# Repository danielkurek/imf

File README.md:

# Interactive mesh framework (IMF)

Framework for interactive distributed network of luminous devices. Devices are based on ESP32-S3. Framework was developed as part of bachelor thesis at Charles University Faculty of Mathematics and Physics (Prague, Czech Republic).

Author: Daniel Kurek 09.05.2024

## Folder structure

- `boards` - source files for devices designed for this framework (official dev modules can also be used)
- `distance-analysis` - analysis of WiFi FTM distance measurement (with measured data)
- `mesh-visualizer` - helper application for visualization of positions of devices and control states of devices through Bluetooth mesh
- `result` - results from testing of the framework on example application
- `src` - source code of the framework

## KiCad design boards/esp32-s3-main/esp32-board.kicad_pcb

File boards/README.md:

# Boards

Boards were designed in KiCAD 7 (then converted to KiCAD 8). In folders `esp32-s3-main` and `esp32-s3-simple` are source files for boards along with exported schematics to PDF, exported BOM and gerbers ready for manufacturing.

`esp32-s3-main` contains board that is used in this work as main module and `esp32-s3-simple` is used as secondary module.

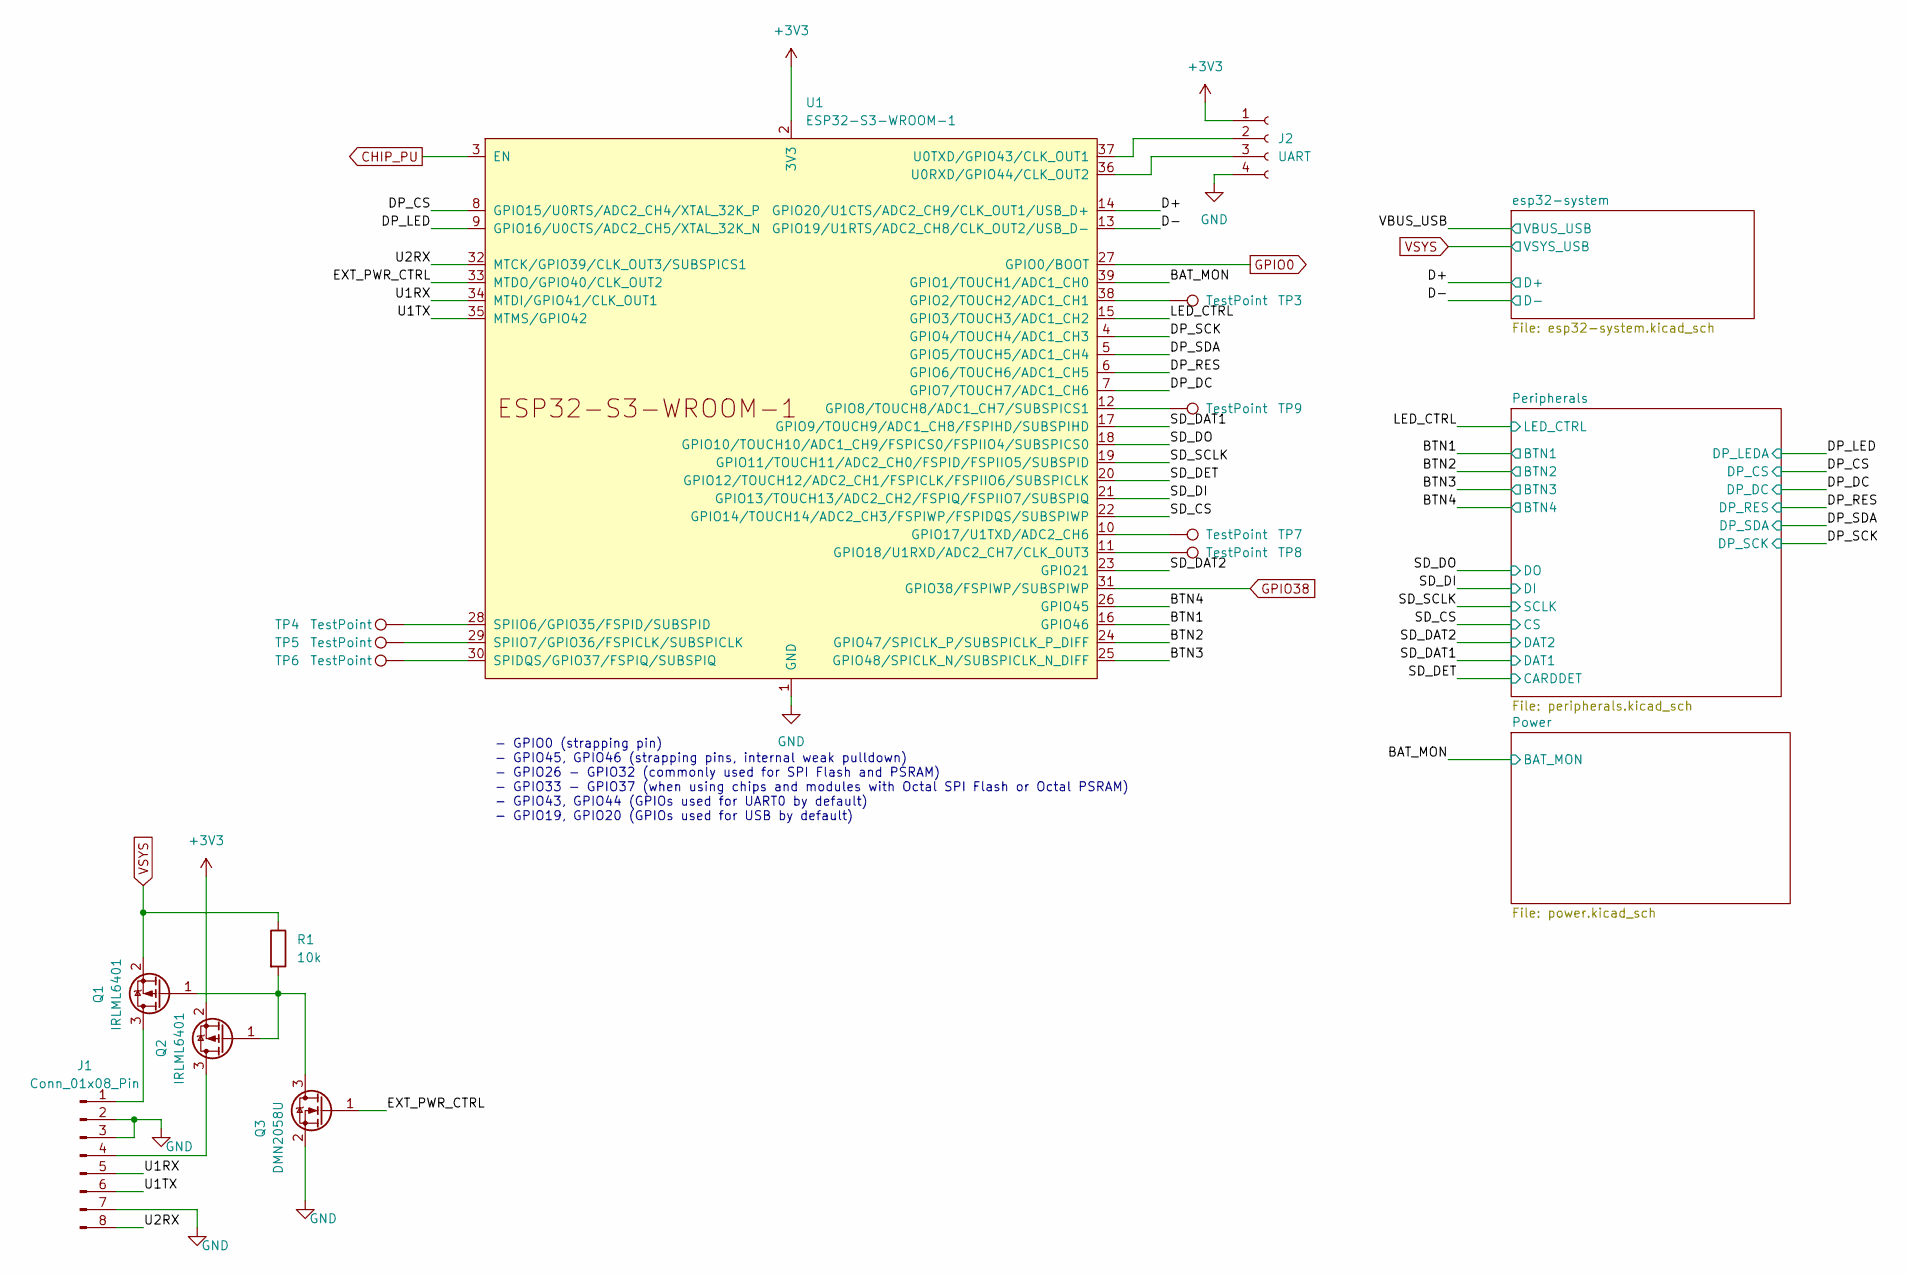
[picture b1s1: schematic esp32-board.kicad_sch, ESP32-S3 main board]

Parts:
J1: Conn_01x08_Pin; PinSocket_1x08_P2.54mm_Vertical
J2: UART; PinSocket_1x04_P2.54mm_Vertical
Q1, Q2: IRLML6401; SOT-23
Q3: DMN2058U; SOT-23
R1: 10k; R_1206_3216Metric_Pad1.30x1.75mm_HandSolder
TP3, TP4, TP5, TP6, TP7, TP8, TP9: TestPoint; TestPoint_Pad_1.0x1.0mm
U1: ESP32-S3-WROOM-1

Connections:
+3V3: J2.1, Q2.2 (S), U1.2 (3V3); also elsewhere on the board
/BAT_MON: U1.39 (GPIO1/TOUCH1/ADC1_CH0); also elsewhere on the board
/BTN1: U1.16 (GPIO46); also elsewhere on the board
/BTN2: U1.24 (GPIO47/SPICLK_P/SUBSPICLK_P_DIFF); also elsewhere on the board
/BTN3: U1.25 (GPIO48/SPICLK_N/SUBSPICLK_N_DIFF); also elsewhere on the board
/BTN4: U1.26 (GPIO45); also elsewhere on the board
/D+: U1.14 (GPIO20/U1CTS/ADC2_CH9/CLK_OUT1/USB_D+); also elsewhere on the board
/D-: U1.13 (GPIO19/U1RTS/ADC2_CH8/CLK_OUT2/USB_D-); also elsewhere on the board
/DP_CS: U1.8 (GPIO15/U0RTS/ADC2_CH4/XTAL_32K_P); also elsewhere on the board
/DP_DC: U1.7 (GPIO7/TOUCH7/ADC1_CH6); also elsewhere on the board
/DP_LED: U1.9 (GPIO16/U0CTS/ADC2_CH5/XTAL_32K_N); also elsewhere on the board
/DP_RES: U1.6 (GPIO6/TOUCH6/ADC1_CH5); also elsewhere on the board
/DP_SCK: U1.4 (GPIO4/TOUCH4/ADC1_CH3); also elsewhere on the board
/DP_SDA: U1.5 (GPIO5/TOUCH5/ADC1_CH4); also elsewhere on the board
/EXT_PWR_CTRL: Q3.1 (G), U1.33 (MTDO/GPIO40/CLK_OUT2)
/LED_CTRL: U1.15 (GPIO3/TOUCH3/ADC1_CH2); also elsewhere on the board
/SD_CS: U1.22 (GPIO14/TOUCH14/ADC2_CH3/FSPIWP/FSPIDQS/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); also elsewhere on the board
/SD_DAT1: U1.17 (GPIO9/TOUCH9/ADC1_CH8/FSPIHD/SUBSPIHD); also elsewhere on the board
/SD_DAT2: U1.23 (GPIO21); also elsewhere on the board
/SD_DET: U1.20 (GPIO12/TOUCH12/ADC2_CH1/FSPICLK/FSPIIO6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); also elsewhere on the board
/SD_DI: U1.21 (GPIO13/TOUCH13/ADC2_CH2/FSPIQ/FSPIIO7/S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); also elsewhere on the board
/SD_DO: U1.18 (GPIO10/TOUCH10/ADC1_CH9/FSPICS0/FSPIIO4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); also elsewhere on the board
/SD_SCLK: U1.19 (GPIO11/TOUCH11/ADC2_CH0/FSPID/FSPIIO5/S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); also elsewhere on the board
/U1RX: J1.5, U1.34 (MTDI/GPIO41/CLK_OUT1)
/U1TX: J1.6, U1.35 (MTMS/GPIO42)
/U2RX: J1.8, U1.32 (MTCK/GPIO39/CLK_OUT3/SUBSPICS1)
CHIP_PU: U1.3 (EN); also elsewhere on the board
GND: J1.2, J1.3, J1.7, J2.4, Q3.2 (S), U1.1 (GND), U1.40 (GND), U1.41 (GND); also elsewhere on the board
GPIO0: U1.27 (GPIO0/BOOT); also elsewhere on the board
GPIO38: U1.31 (GPIO38/FSPIWP/SUBSPIWP); also elsewhere on the board
unnamed: J1.1, Q1.3 (D)
unnamed: J1.4, Q2.3 (D)
unnamed: J2.2, U1.37 (U0TXD/GPIO43/CLK_OUT1)
unnamed: J2.3, U1.36 (U0RXD/GPIO44/CLK_OUT2)
unnamed: Q1.1 (G), Q2.1 (G), Q3.3 (D), R1.2
unnamed: TP3.1, U1.38 (GPIO2/TOUCH2/ADC1_CH1)
unnamed: TP9.1, U1.12 (GPIO8/TOUCH8/ADC1_CH7/SUBSPICS1)
unnamed: TP7.1, U1.10 (GPIO17/U1TXD/ADC2_CH6)
unnamed: TP8.1, U1.11 (GPIO18/U1RXD/ADC2_CH7/CLK_OUT3)
unnamed: TP6.1, U1.30 (SPIDQS/GPIO37/FSPIQ/SUBSPIQ)
unnamed: TP4.1, U1.28 (SPIIO6/GPIO35/FSPID/SUBSPID)
unnamed: TP5.1, U1.29 (SPIIO7/GPIO36/FSPICLK/SUBSPICLK)
VSYS: Q1.2 (S), R1.1; also elsewhere on the board

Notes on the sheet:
- GPIO0 (strapping pin) - GPIO45, GPIO46 (strapping pins, internal weak pulldown) - GPIO26 - GPIO32 (commonly used for SPI Flash and PSRAM) - GPIO33 - GPIO37 (when using chips and modules with Octal SPI Flash or Octal PSRAM) - GPIO43, GPIO44 (GPIOs used for UART0 by default) - GPIO19, GPIO20 (GPIOs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

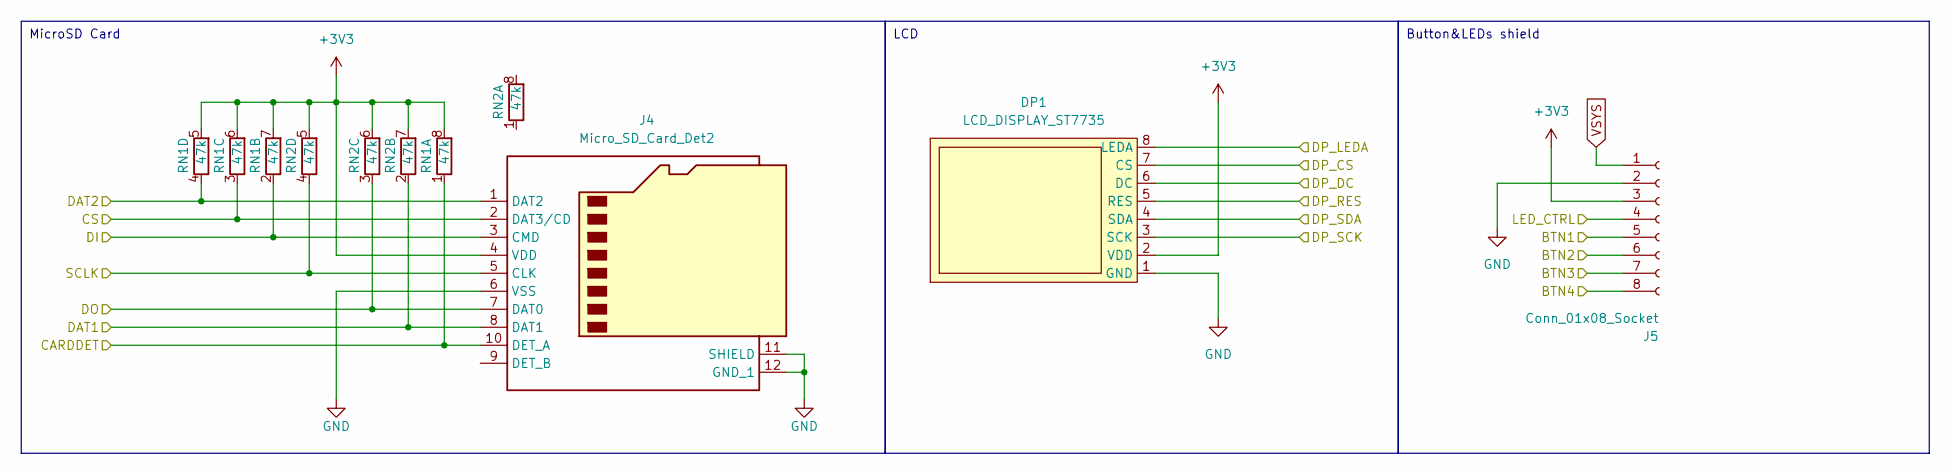
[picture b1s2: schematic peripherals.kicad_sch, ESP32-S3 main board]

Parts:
DP1: LCD_DISPLAY_ST7735; PinSocket_1x08_P2.54mm_Vertical
J4: Micro_SD_Card_Det2; GCT_MEM2061-01-188-00-A_REVA
J5: Conn_01x08_Socket; PinSocket_1x08_P2.54mm_Vertical
RN1, RN2: 47k; R_Array_Convex_4x1206

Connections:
+3V3: DP1.2 (VDD), J4.4 (VDD), J5.3, RN1.5 (R4.2), RN1.6 (R3.2), RN1.7 (R2.2), RN1.8 (R1.2), RN2.5 (R4.2), RN2.6 (R3.2), RN2.7 (R2.2); also elsewhere on the board
/BTN1: J5.5; also elsewhere on the board
/BTN2: J5.6; also elsewhere on the board
/BTN3: J5.7; also elsewhere on the board
/BTN4: J5.8; also elsewhere on the board
/DP_CS: DP1.7 (CS); also elsewhere on the board
/DP_DC: DP1.6 (DC); also elsewhere on the board
/DP_LED: DP1.8 (LEDA); also elsewhere on the board
/DP_RES: DP1.5 (RES); also elsewhere on the board
/DP_SCK: DP1.3 (SCK); also elsewhere on the board
/DP_SDA: DP1.4 (SDA); also elsewhere on the board
/LED_CTRL: J5.4; also elsewhere on the board
/SD_CS: J4.2 (DAT3/CD), RN1.3 (R3.1); also elsewhere on the board
/SD_DAT1: J4.8 (DAT1), RN2.2 (R2.1); also elsewhere on the board
/SD_DAT2: J4.1 (DAT2), RN1.4 (R4.1); also elsewhere on the board
/SD_DET: J4.10 (DET_A), RN1.1 (R1.1); also elsewhere on the board
/SD_DI: J4.3 (CMD), RN1.2 (R2.1); also elsewhere on the board
/SD_DO: J4.7 (DAT0), RN2.3 (R3.1); also elsewhere on the board
/SD_SCLK: J4.5 (CLK), RN2.4 (R4.1); also elsewhere on the board
GND: DP1.1 (GND), J4.6 (VSS), J4.11 (SHIELD), J4.12 (GND_1), J5.2; also elsewhere on the board
VSYS: J5.1; also elsewhere on the board

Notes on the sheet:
Button&LEDs shield
MicroSD Card
LCD

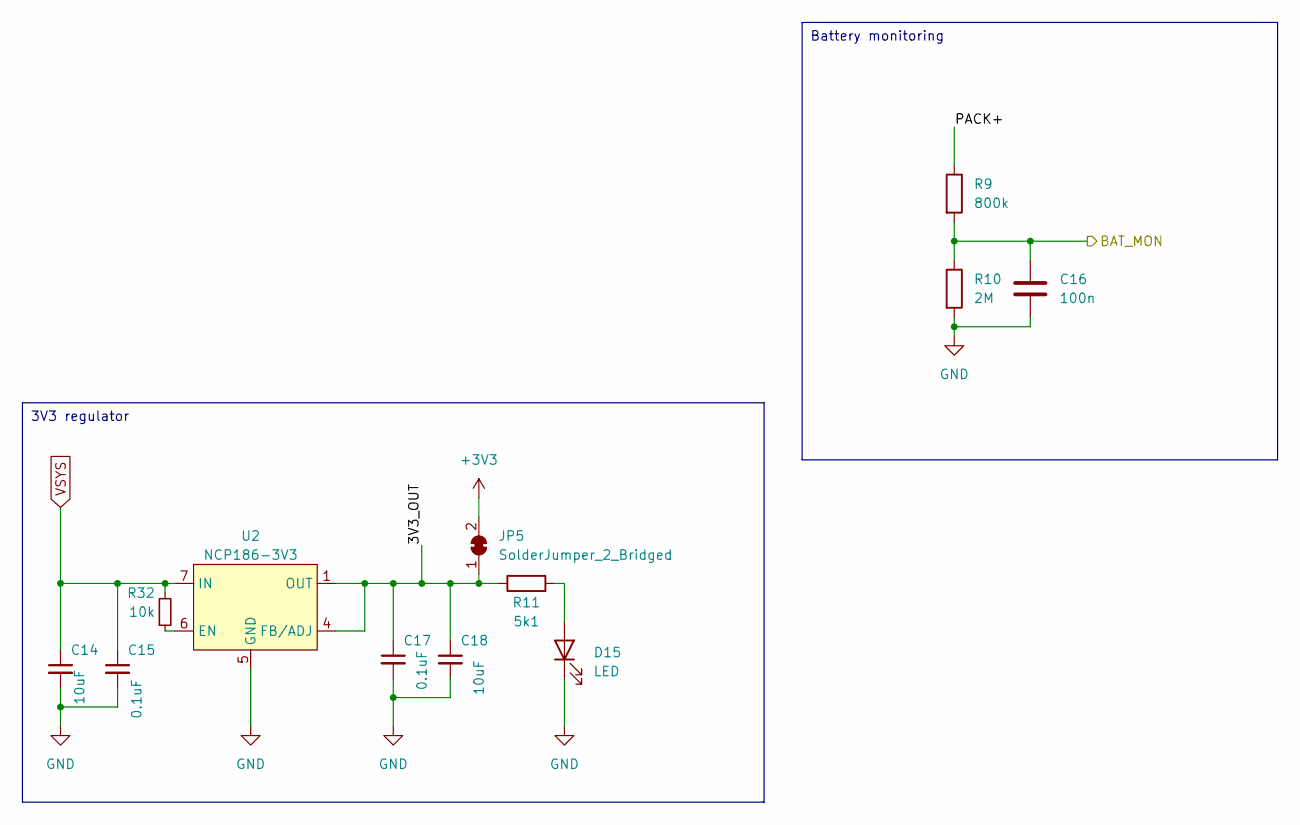
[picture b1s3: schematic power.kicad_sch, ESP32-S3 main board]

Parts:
C14, C18: 10uF; C_1206_3216Metric_Pad1.33x1.80mm_HandSolder; Rating 50V; Tolerance 10%
C15, C17: 0.1uF; C_0603_1608Metric_Pad1.08x0.95mm_HandSolder; Rating 50V; Tolerance 10%
C16: 100n; C_0603_1608Metric_Pad1.08x0.95mm_HandSolder
D15: LED; LED_0805_2012Metric_Pad1.15x1.40mm_HandSolder
JP5: SolderJumper_2_Bridged; SolderJumper-2_P1.3mm_Bridged2Bar_Pad1.0x1.5mm
R9: 800k; R_1206_3216Metric_Pad1.30x1.75mm_HandSolder
R10: 2M; R_1206_3216Metric_Pad1.30x1.75mm_HandSolder
R11: 5k1; R_1206_3216Metric_Pad1.30x1.75mm_HandSolder
R32: 10k; R_1206_3216Metric_Pad1.30x1.75mm_HandSolder
U2: NCP186-3V3; XDFN8

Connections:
+3V3: JP5.2 (B); also elsewhere on the board
/BAT_MON: C16.1, R9.2, R10.1; also elsewhere on the board
/Power/3V3_OUT: C17.1, C18.1, JP5.1 (A), R11.1, U2.1 (OUT), U2.2 (OUT), U2.4 (FB/ADJ)
/Power/PACK+: R9.1
GND: C14.2, C15.2, C16.2, C17.2, C18.2, D15.1 (K), R10.2, U2.5 (GND), U2.EPAD (GND); also elsewhere on the board
unnamed: D15.2 (A), R11.2
unnamed: R32.1, U2.6 (EN)
VSYS: C14.1, C15.1, R32.2, U2.7 (IN), U2.8 (IN); also elsewhere on the board

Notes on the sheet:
3V3 regulator
Battery monitoring

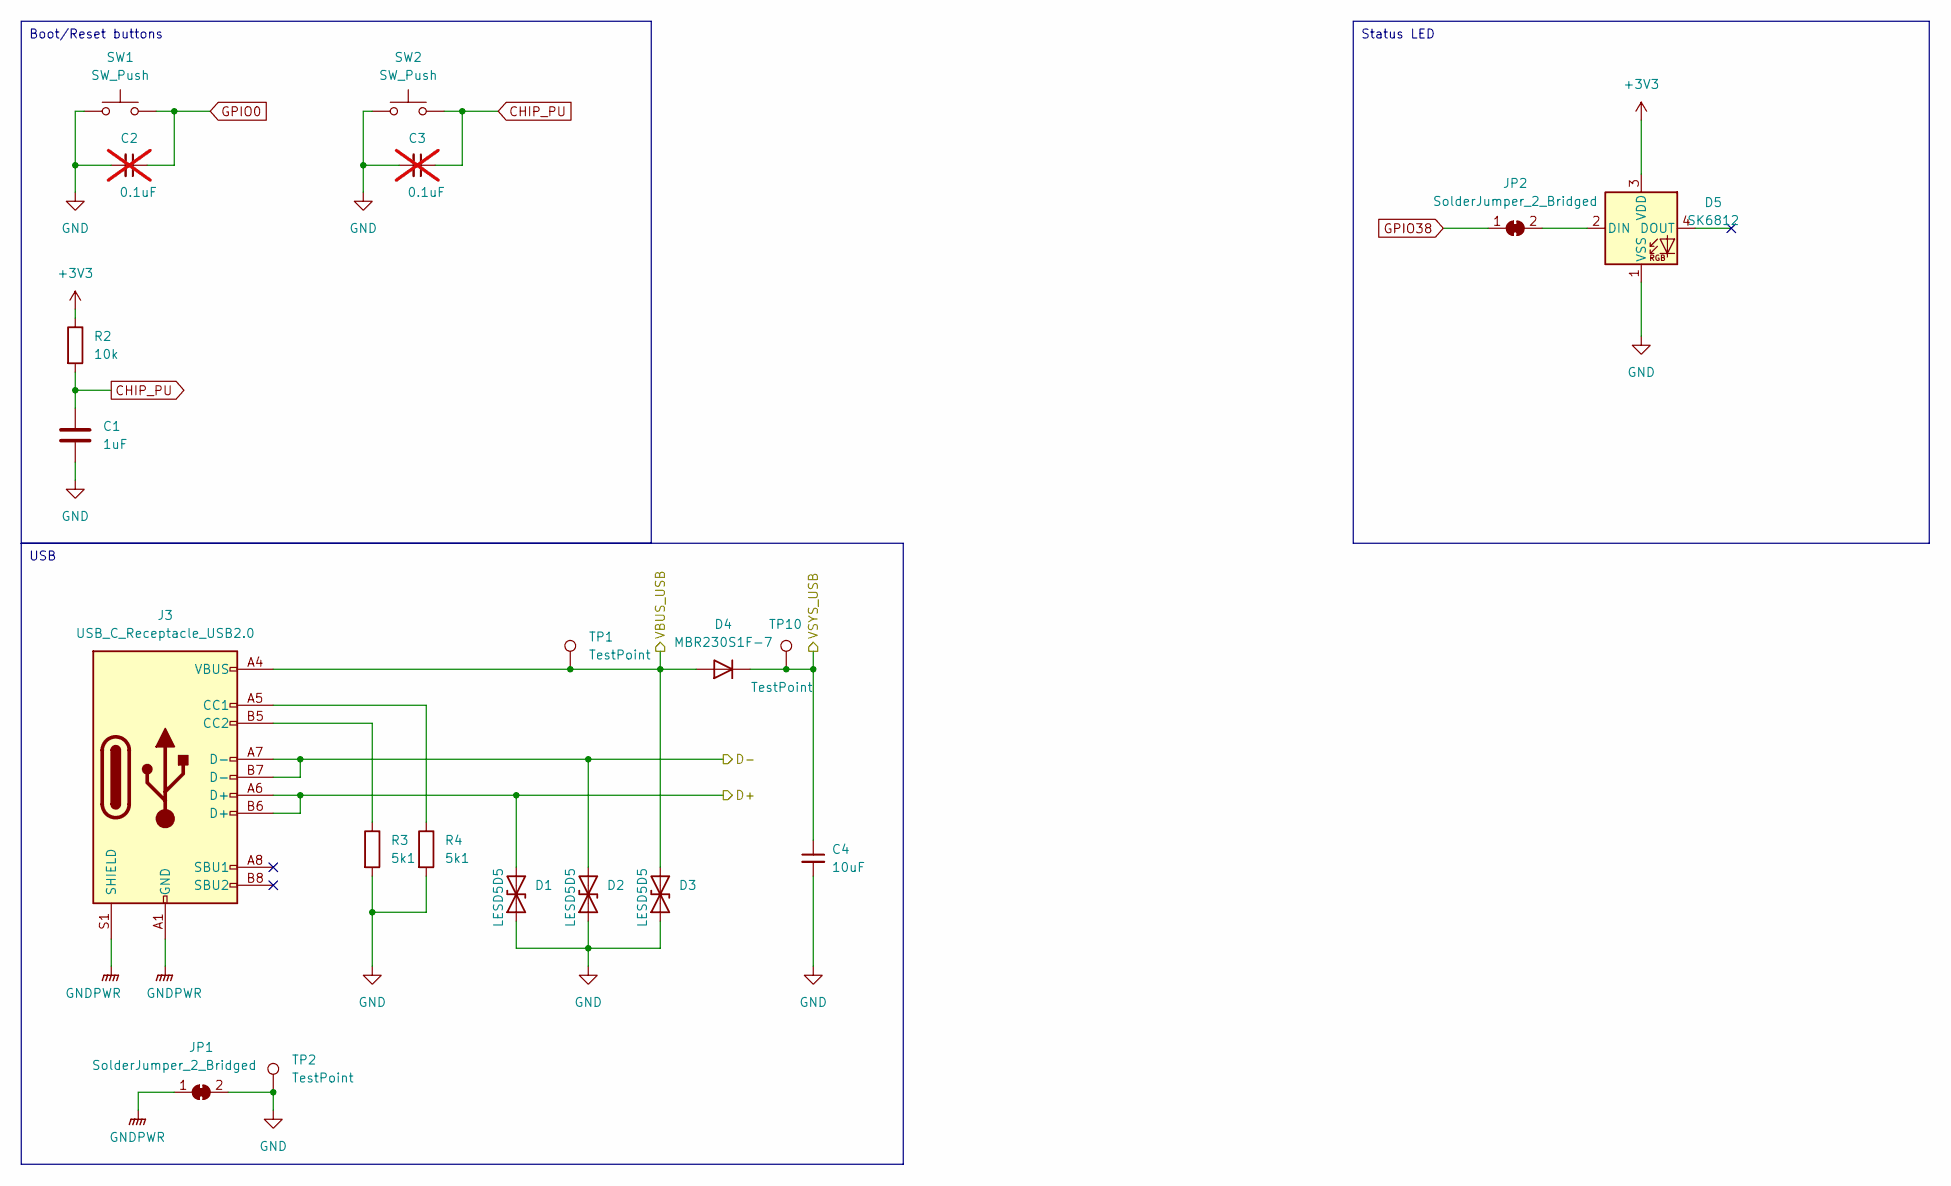
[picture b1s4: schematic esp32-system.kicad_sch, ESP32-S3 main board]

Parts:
C1: 1uF; C_0603_1608Metric_Pad1.08x0.95mm_HandSolder
C2, C3: 0.1uF; C_0603_1608Metric_Pad1.08x0.95mm_HandSolder; Rating 50V; Tolerance 10%; not fitted
C4: 10uF; C_1206_3216Metric_Pad1.33x1.80mm_HandSolder; Rating 25V; Tolerance 20%
D1, D2, D3: LESD5D5; D_SOD-323_HandSoldering
D4: MBR230S1F-7; D_SOD-123F
D5: SK6812; LED_SK6812_PLCC4_5.0x5.0mm_P3.2mm
J3: USB_C_Receptacle_USB2.0; USB_C_Receptacle_GCT_USB4105-xx-A_16P_TopMnt_Horizontal
JP1, JP2: SolderJumper_2_Bridged; SolderJumper-2_P1.3mm_Bridged2Bar_Pad1.0x1.5mm
R2: 10k; R_1206_3216Metric_Pad1.30x1.75mm_HandSolder
R3, R4: 5k1; R_1206_3216Metric_Pad1.30x1.75mm_HandSolder
SW1, SW2: SW_Push; SW_PUSH_6mm
TP1, TP2, TP10: TestPoint; TestPoint_Pad_1.0x1.0mm

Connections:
+3V3: D5.3 (VDD), R2.1; also elsewhere on the board
/D+: D1.2 (A2), J3.A6 (D+), J3.B6 (D+); also elsewhere on the board
/D-: D2.2 (A2), J3.A7 (D-), J3.B7 (D-); also elsewhere on the board
/VBUS_USB: D3.2 (A2), D4.2 (A), J3.A4 (VBUS), J3.A9 (VBUS), J3.B4 (VBUS), J3.B9 (VBUS), TP1.1
CHIP_PU: C1.1, C3.1, R2.2, SW2.2; also elsewhere on the board
GND: C1.2, C2.2, C3.2, C4.2, D1.1 (A1), D2.1 (A1), D3.1 (A1), D5.1 (VSS), JP1.2 (B), R3.2, R4.2, SW1.1, SW2.1, TP2.1; also elsewhere on the board
GNDPWR: J3.A1 (GND), J3.A12 (GND), J3.B1 (GND), J3.B12 (GND), J3.S1 (SHIELD), JP1.1 (A)
GPIO0: C2.1, SW1.2; also elsewhere on the board
GPIO38: JP2.1 (A); also elsewhere on the board
unnamed: D5.2 (DIN), JP2.2 (B)
unnamed: J3.A5 (CC1), R4.1
unnamed: J3.B5 (CC2), R3.1
VSYS: C4.1, D4.1 (K), TP10.1; also elsewhere on the board

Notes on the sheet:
Status LED
USB
Boot/Reset buttons

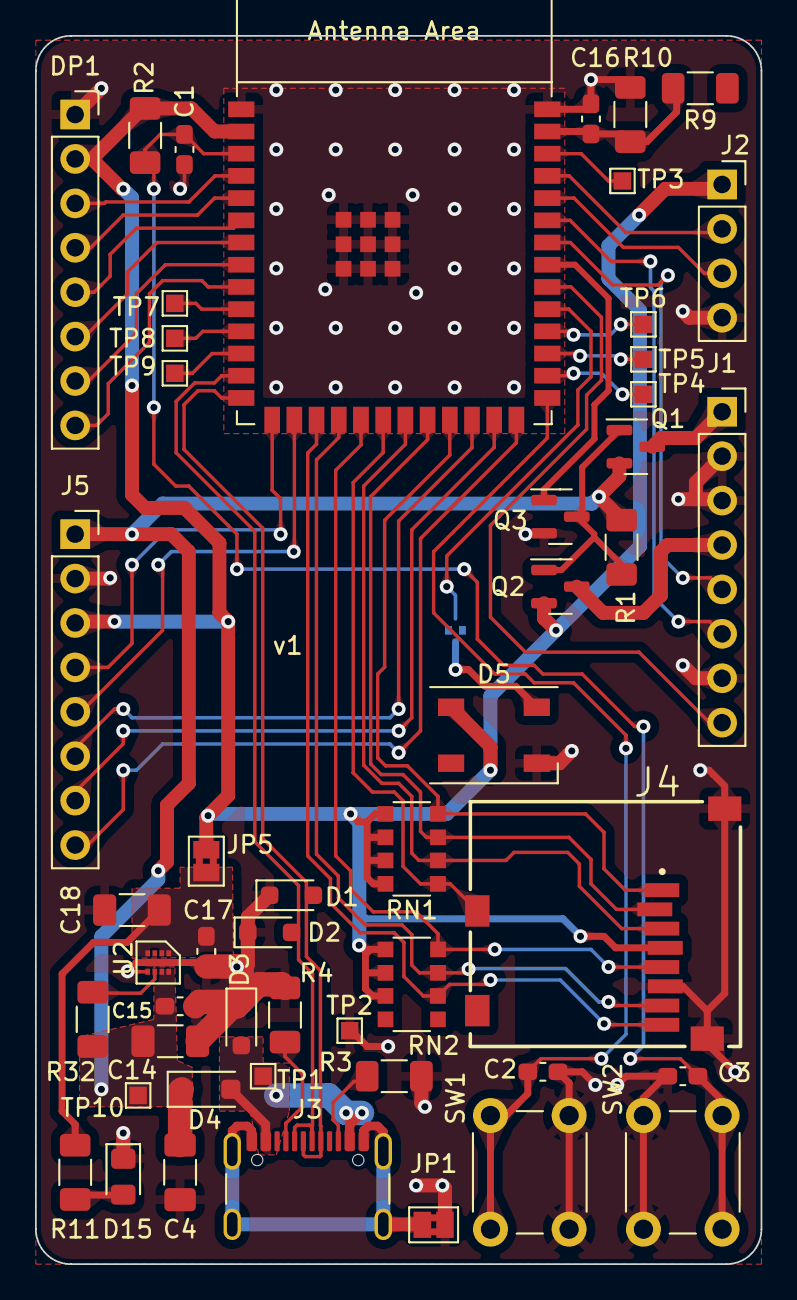
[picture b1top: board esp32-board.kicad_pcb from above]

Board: 2 copper layers, 41.5 x 70.2 mm, 51 parts (1 on the bottom side), 51 nets.

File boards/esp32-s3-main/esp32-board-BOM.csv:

"Source:","/home/dk/Projects/KiCAD projects/esp32-board/esp32-board.kicad_sch"
"Date:","Tue 26 Mar 2024 17:12:36 CET"
"Tool:","Eeschema 7.0.11-2.fc39"
"Generator:","/usr/share/kicad/plugins/bom_csv_grouped_by_value.py"
"Component Count:","51"

"Collated Components:"

"Item","Qty","Reference(s)","Value","LibPart","Footprint","Datasheet","DNP","Rating","Sim.Device","Sim.Pins","Tolerance"
"1","1","C1","1uF","Device:C","Capacitor_SMD:C_0603_1608Metric_Pad1.08x0.95mm_HandSolder","~","","","","",""
"2","2","C2, C3","0.1uF","Device:C_Small","Capacitor_SMD:C_0603_1608Metric_Pad1.08x0.95mm_HandSolder","~","DNP","50V","","","10%"
"3","3","C4, C14, C18","10uF","Device:C_Small","Capacitor_SMD:C_1206_3216Metric_Pad1.33x1.80mm_HandSolder","~","","25V","","","20%"
"4","2","C15, C17","0.1uF","Device:C_Small","Capacitor_SMD:C_0603_1608Metric_Pad1.08x0.95mm_HandSolder","~","","50V","","","10%"
"5","1","C16","100n","Device:C","Capacitor_SMD:C_0603_1608Metric_Pad1.08x0.95mm_HandSolder","~","","","","",""
"6","3","D1, D2, D3","LESD5D5","Device:D_TVS","Diode_SMD:D_SOD-323_HandSoldering","~","","","","",""
"7","1","D4","MBR230S1F-7 ","Device:D","Diode_SMD:D_SOD-123F","~","","","D","1=K 2=A",""
"8","1","D5","SK6812","LED:SK6812","LED_SMD:LED_SK6812_PLCC4_5.0x5.0mm_P3.2mm","https://cdn-shop.adafruit.com/product-files/1138/SK6812+LED+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","","","","",""
"9","1","D15","LED","Device:LED","LED_SMD:LED_0805_2012Metric_Pad1.15x1.40mm_HandSolder","~","","","","",""
"10","1","DP1","LCD_DISPLAY_ST7735","Custom_lib:LCD_DISPLAY_ST7735","Connector_PinSocket_2.54mm:PinSocket_1x08_P2.54mm_Vertical","","","","","",""
"11","1","J1","Conn_01x08_Pin","Connector:Conn_01x08_Pin","Connector_PinSocket_2.54mm:PinSocket_1x08_P2.54mm_Vertical","~","","","","",""
"12","1","J2","UART","Connector:Conn_01x04_Socket","Connector_PinSocket_2.54mm:PinSocket_1x04_P2.54mm_Vertical","~","","","","",""
"13","1","J3","USB_C_Receptacle_USB2.0","Connector:USB_C_Receptacle_USB2.0","Connector_USB:USB_C_Receptacle_GCT_USB4105-xx-A_16P_TopMnt_Horizontal","https://www.usb.org/sites/default/files/documents/usb_type-c.zip","","","","",""
"14","1","J4","Micro_SD_Card_Det2",":Micro_SD_Card_Det2_1","GCT_MEM2061:GCT_MEM2061-01-188-00-A_REVA","https://gct.co/pdfjs/web/viewer.html?file=/files/specs/MEM20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","","","","",""
"15","1","J5","Conn_01x08_Socket","Connector:Conn_01x08_Socket","Connector_PinSocket_2.54mm:PinSocket_1x08_P2.54mm_Vertical","~","","","","",""
"16","3","JP1, JP2, JP5","SolderJumper_2_Bridged","Jumper:SolderJumper_2_Bridged","Jumper:SolderJumper-2_P1.3mm_Bridged2Bar_Pad1.0x1.5mm","~","","","","",""
"17","2","Q1, Q2","IRLML6401","Transistor_FET:IRLML6401","Package_TO_SOT_SMD:SOT-23","https://www.infineon.com/dgdl/irlml6401pbf.pdf?fileId=5546d4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","","","","",""
"18","1","Q3","DMN2058U","Transistor_FET:DMN2058U","Package_TO_SOT_SMD:SOT-23","http://www.diodes.com/assets/Datasheets/DMN2058U.pdf","","","","",""
"19","2","R1, R2","10k","Device:R","Resistor_SMD:R_1206_3216Metric_Pad1.30x1.75mm_HandSolder","~","","","","",""
"20","3","R3, R4, R11","5k1","Device:R","Resistor_SMD:R_1206_3216Metric_Pad1.30x1.75mm_HandSolder","~","","","","",""
"21","1","R9","800k","Device:R","Resistor_SMD:R_1206_3216Metric_Pad1.30x1.75mm_HandSolder","~","","","","",""
"22","1","R10","2M","Device:R","Resistor_SMD:R_1206_3216Metric_Pad1.30x1.75mm_HandSolder","~","","","","",""
"23","1","R32","10k","Device:R_Small","Resistor_SMD:R_1206_3216Metric_Pad1.30x1.75mm_HandSolder","~","","","","",""
"24","2","RN1, RN2","47k","Device:R_Pack04_Split","Resistor_SMD:R_Array_Convex_4x1206","~","","","","",""
"25","2","SW1, SW2","SW_Push","Switch:SW_Push","Button_Switch_THT:SW_PUSH_6mm","~","","","","",""
"26","10","TP1, TP2, TP3, TP4, TP5, TP6, TP7, TP8, TP9, TP10","TestPoint","Connector:TestPoint","TestPoint:TestPoint_Pad_1.0x1.0mm","~","","","","",""
"27","1","U1","ESP32-S3-WROOM-1","PCM_Espressif:ESP32-S3-WROOM-1","PCM_Espressif:ESP32-S3-WROOM-1","https://www.espressif.com/sites/default/files/documentation/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","","","","",""
"28","1","U2","NCP186-3V3","Custom_lib:NCP186-3V3","Custom:XDFN8","https://www.onsemi.com/pdf/datasheet/ncp186-d.pdf","","","","",""

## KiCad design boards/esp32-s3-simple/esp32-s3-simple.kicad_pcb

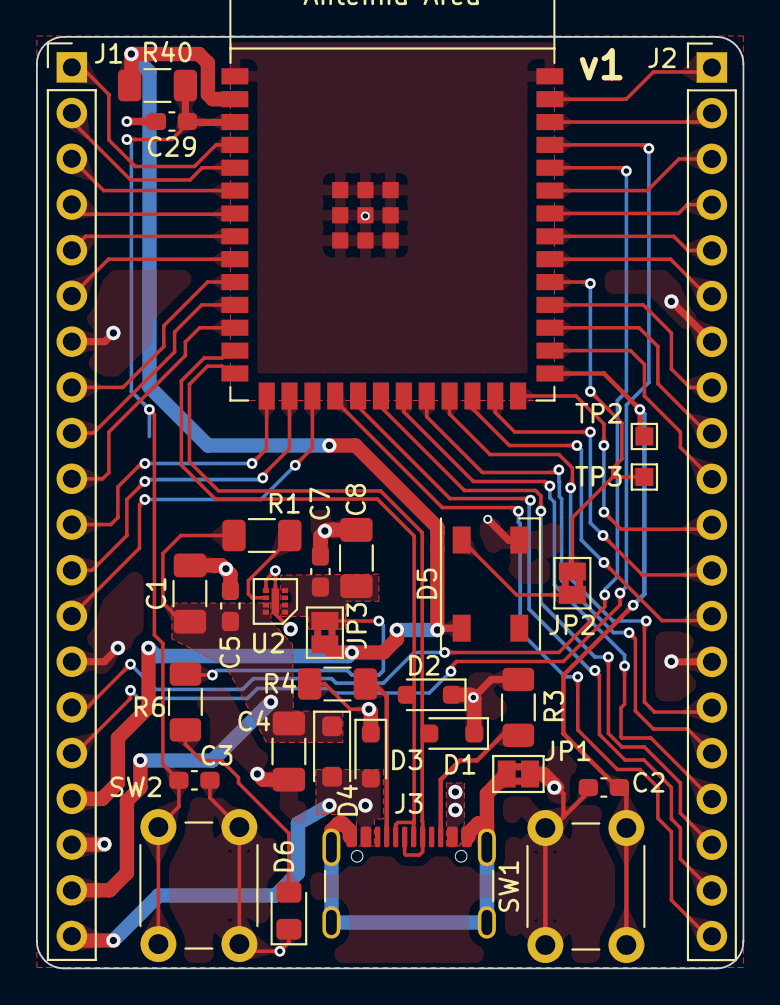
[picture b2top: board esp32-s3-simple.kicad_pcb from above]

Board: 2 copper layers, 39.2 x 51.8 mm, 32 parts (1 on the bottom side), 48 nets.

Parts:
C1, C4, C8: 10uF; C_1206_3216Metric_Pad1.33x1.80mm_HandSolder
C2, C3, C5, C7: 0.1uF; C_0603_1608Metric_Pad1.08x0.95mm_HandSolder
C29: 1uF; C_0603_1608Metric_Pad1.08x0.95mm_HandSolder
D1, D2, D3: LESD5D5; D_SOD-323_HandSoldering
D4: MBR230S1F-7; D_SOD-123F
D5: SK6812; LED_SK6812_PLCC4_5.0x5.0mm_P3.2mm
D6: LED; LED_0805_2012Metric_Pad1.15x1.40mm_HandSolder
J1, J2: Conn_01x20_Pin; PinHeader_1x20_P2.54mm_Vertical
J3: USB_C_Receptacle_USB2.0; USB_C_Receptacle_GCT_USB4105-xx-A_16P_TopMnt_Horizontal
JP1, JP2, JP3: SolderJumper_2_Bridged; SolderJumper-2_P1.3mm_Bridged2Bar_Pad1.0x1.5mm
R1, R40: 10k; R_1206_3216Metric_Pad1.30x1.75mm_HandSolder
R3, R4, R6: 5k1; R_1206_3216Metric_Pad1.30x1.75mm_HandSolder
SW1, SW2: SW_Push; SW_PUSH_6mm
TP1, TP2, TP3: TestPoint; TestPoint_Pad_1.0x1.0mm
U1: ESP32-S3-WROOM-1
U2: NCP186-3V3; XDFN8

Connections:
+3V3: D5.3 (VDD), J1.17, JP3.2 (B), R40.1, U1.2 (3V3)
/D+: D1.2 (A2), J3.A6 (D+), J3.B6 (D+), U1.14 (GPIO20/U1CTS/ADC2_CH9/CLK_OUT1/USB_D+)
/D-: D2.2 (A2), J3.A7 (D-), J3.B7 (D-), U1.13 (GPIO19/U1RTS/ADC2_CH8/CLK_OUT2/USB_D-)
/GPIO1: J2.1, U1.39 (GPIO1/TOUCH1/ADC1_CH0)
/GPIO2: J2.2, U1.38 (GPIO2/TOUCH2/ADC1_CH1)
/GPIO3: J1.11, U1.15 (GPIO3/TOUCH3/ADC1_CH2)
/GPIO4: J1.1, U1.4 (GPIO4/TOUCH4/ADC1_CH3)
/GPIO5: J1.2, U1.5 (GPIO5/TOUCH5/ADC1_CH4)
/GPIO6: J1.3, U1.6 (GPIO6/TOUCH6/ADC1_CH5)
/GPIO7: J1.4, U1.7 (GPIO7/TOUCH7/ADC1_CH6)
/GPIO8: J1.10, U1.12 (GPIO8/TOUCH8/ADC1_CH7/SUBSPICS1)
/GPIO9: J1.13, U1.17 (GPIO9/TOUCH9/ADC1_CH8/FSPIHD/SUBSPIHD)
/GPIO10: J2.20, U1.18 (GPIO10/TOUCH10/ADC1_CH9/FSPICS0/FSPIIO4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)
/GPIO11: J2.19, U1.19 (GPIO11/TOUCH11/ADC2_CH0/FSPID/FSPIIO5/S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)
/GPIO12: J2.18, U1.20 (GPIO12/TOUCH12/ADC2_CH1/FSPICLK/FSPIIO6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)
/GPIO13: J2.17, U1.21 (GPIO13/TOUCH13/ADC2_CH2/FSPIQ/FSPIIO7/S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)
/GPIO14: J2.16, U1.22 (GPIO14/TOUCH14/ADC2_CH3/FSPIWP/FSPIDQS/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)
/GPIO15: J1.5, U1.8 (GPIO15/U0RTS/ADC2_CH4/XTAL_32K_P)
/GPIO16: J1.6, U1.9 (GPIO16/U0CTS/ADC2_CH5/XTAL_32K_N)
/GPIO17: J1.8, U1.10 (GPIO17/U1TXD/ADC2_CH6)
/GPIO18: J1.9, U1.11 (GPIO18/U1RXD/ADC2_CH7/CLK_OUT3)
/GPIO21: J2.15, U1.23 (GPIO21)
/GPIO35: J2.10, U1.28 (SPIIO6/GPIO35/FSPID/SUBSPID)
/GPIO36: J2.9, U1.29 (SPIIO7/GPIO36/FSPICLK/SUBSPICLK)
/GPIO37: J2.8, U1.30 (SPIDQS/GPIO37/FSPIQ/SUBSPIQ)
/GPIO39: J2.6, U1.32 (MTCK/GPIO39/CLK_OUT3/SUBSPICS1)
/GPIO40: J2.5, U1.33 (MTDO/GPIO40/CLK_OUT2)
/GPIO41: J2.4, U1.34 (MTDI/GPIO41/CLK_OUT1)
/GPIO42: J2.3, U1.35 (MTMS/GPIO42)
/GPIO45: J2.11, U1.26 (GPIO45)
/GPIO46: J1.12, U1.16 (GPIO46)
/GPIO47: J2.13, U1.24 (GPIO47/SPICLK_P/SUBSPICLK_P_DIFF)
/GPIO48: J2.12, U1.25 (GPIO48/SPICLK_N/SUBSPICLK_N_DIFF)
/RX: J1.15, U1.36 (U0RXD/GPIO44/CLK_OUT2)
/TX: J1.16, U1.37 (U0TXD/GPIO43/CLK_OUT1)
/VBUS_USB: D3.2 (A2), D4.2 (A), J1.20, J3.A4 (VBUS), J3.A9 (VBUS), J3.B4 (VBUS), J3.B9 (VBUS)
/power/3V3_OUT: C7.1, C8.1, JP3.1 (A), R6.1, U2.1 (OUT), U2.2 (OUT), U2.4 (FB/ADJ)
CHIP_PU: C3.1, C29.1, R40.2, SW2.2, TP1.1, U1.3 (EN)
GND: C1.2, C2.2, C3.2, C4.2, C5.2, C7.2, C8.2, C29.2, D1.1 (A1), D2.1 (A1), D3.1 (A1), D5.1 (VSS), D6.1 (K), J1.7, J1.14, J1.18, J2.7, J2.14, JP1.2 (B), R3.2, R4.2, SW1.1, SW2.1, U1.1 (GND), U1.40 (GND), U1.41 (GND), U2.5 (GND), U2.EPAD (GND)
GNDPWR: J3.A1 (GND), J3.A12 (GND), J3.B1 (GND), J3.B12 (GND), J3.S1 (SHIELD), JP1.1 (A)
GPIO0: C2.1, SW1.2, TP2.1, U1.27 (GPIO0/BOOT)
GPIO38: JP2.1 (A), TP3.1, U1.31 (GPIO38/FSPIWP/SUBSPIWP)
unnamed: D5.2 (DIN), JP2.2 (B)
unnamed: D6.2 (A), R6.2
unnamed: J3.A5 (CC1), R4.1
unnamed: J3.B5 (CC2), R3.1
unnamed: R1.1, U2.6 (EN)
VSYS: C1.1, C4.1, C5.1, D4.1 (K), J1.19, R1.2, U2.7 (IN), U2.8 (IN)

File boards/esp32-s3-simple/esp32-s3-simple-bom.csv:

"Source:","/home/dk/Projects/KiCAD projects/esp32-s3-simple/esp32-s3-simple.kicad_sch"
"Date:","Sun 05 Nov 2023 17:30:14 CET"
"Tool:","Eeschema 7.0.8-1.fc38"
"Generator:","/usr/share/kicad/plugins/bom_csv_grouped_by_value.py"
"Component Count:","32"

"Collated Components:"

"Item","Qty","Reference(s)","Value","LibPart","Footprint","Datasheet","DNP","Rating","Sim.Device","Sim.Pins","Tolerance"
"1","3","C1, C4, C8","10uF","Device:C_Small","Capacitor_SMD:C_1206_3216Metric_Pad1.33x1.80mm_HandSolder","~","","50V","","","10%"
"2","2","C2, C3","0.1uF","Device:C_Small","Capacitor_SMD:C_0603_1608Metric_Pad1.08x0.95mm_HandSolder","~","DNP","50V","","","10%"
"3","2","C5, C7","0.1uF","Device:C_Small","Capacitor_SMD:C_0603_1608Metric_Pad1.08x0.95mm_HandSolder","~","","50V","","","10%"
"4","1","C29","1uF","Device:C","Capacitor_SMD:C_0603_1608Metric_Pad1.08x0.95mm_HandSolder","~","","","","",""
"5","3","D1, D2, D3","LESD5D5","Device:D_TVS","Diode_SMD:D_SOD-323_HandSoldering","~","","","","",""
"6","1","D4","MBR230S1F-7","Device:D","Diode_SMD:D_SOD-123F","~","","","D","1=K 2=A",""
"7","1","D5","SK6812","LED:SK6812","LED_SMD:LED_SK6812_PLCC4_5.0x5.0mm_P3.2mm","https://cdn-shop.adafruit.com/product-files/1138/SK6812+LED+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","","","","",""
"8","1","D6","LED","Device:LED","LED_SMD:LED_0805_2012Metric_Pad1.15x1.40mm_HandSolder","~","","","","",""
"9","2","J1, J2","Conn_01x20_Pin","Connector:Conn_01x20_Pin","Connector_PinHeader_2.54mm:PinHeader_1x20_P2.54mm_Vertical","~","","","","",""
"10","1","J3","USB_C_Receptacle_USB2.0","Connector:USB_C_Receptacle_USB2.0","Connector_USB:USB_C_Receptacle_GCT_USB4105-xx-A_16P_TopMnt_Horizontal","https://www.usb.org/sites/default/files/documents/usb_type-c.zip","","","","",""
"11","3","JP1, JP2, JP3","SolderJumper_2_Bridged","Jumper:SolderJumper_2_Bridged","Jumper:SolderJumper-2_P1.3mm_Bridged2Bar_Pad1.0x1.5mm","~","","","","",""
"12","1","R1","10k","Device:R_Small","Resistor_SMD:R_1206_3216Metric_Pad1.30x1.75mm_HandSolder","~","","","","",""
"13","3","R3, R4, R6","5k1","Device:R","Resistor_SMD:R_1206_3216Metric_Pad1.30x1.75mm_HandSolder","~","","","","",""
"14","1","R40","10k","Device:R","Resistor_SMD:R_1206_3216Metric_Pad1.30x1.75mm_HandSolder","~","","","","",""
"15","2","SW1, SW2","SW_Push","Switch:SW_Push","Button_Switch_THT:SW_PUSH_6mm","~","","","","",""
"16","3","TP1, TP2, TP3","TestPoint","Connector:TestPoint","TestPoint:TestPoint_Pad_1.0x1.0mm","~","","","","",""
"17","1","U1","ESP32-S3-WROOM-1","PCM_Espressif:ESP32-S3-WROOM-1","PCM_Espressif:ESP32-S3-WROOM-1","https://www.espressif.com/sites/default/files/documentation/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","","","","",""
"18","1","U2","NCP186-3V3","Custom_lib:NCP186-3V3","Custom:XDFN8","https://www.onsemi.com/pdf/datasheet/ncp186-d.pdf","","","","",""
